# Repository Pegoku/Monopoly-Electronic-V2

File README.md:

# Monopoly-Electronic-V2
This is a recreation of the classic Monopoly Electronic Banking game using modern technology. The project utilizes an ESP32 microcontroller to handle game logic and interactions, along with a Touch LCD display and RFID readers for player identification and transactions.

## Demo

[Demo Video](https://youtube.com/shorts/_shUK3fcT8k?feature=share)

## Images

### Final product

### CAD

<details>
<summary>Xray view - click to expand</summary>

</details>

### PCB

<details>
<summary>Schematic - click to expand</summary>

</details>

## Features
- Electronic banking system using RFID cards for a more reliable process.
- Support for multiple players with individual RFID cards.
- Real-time game state updates displayed on the LCD.
- Sound effects for an immersive gaming experience.
- Customizable game rules and settings.

## UI

### Player registration

### Main game screen

### Card interaction

## How the Game Works

Gameplay focuses on **NFC interaction instead of menus**.

Players throw the dice, and depending on where they land, they interact with the game console using their RFID cards. For example, if a player lands on a property, they can use their card to purchase it, or pay rent.

The game keeps track of each player's balance and properties, and updates the display accordingly. The use of RFID cards allows for a more seamless and engaging gaming experience, as players can quickly and easily interact with the game without navigating through complex menus. 

When a player has not enough money to pay rent or buy a property, they can choose to mortgage their properties or declare bankruptcy. The game will automatically handle these situations and update the game state accordingly.

If a player doesn't have enough money to pay rent, they will be bankrupt and removed from the game. The last player remaining with money wins the game.

### Card programming

To program the RFID cards, you can use the programming mode in the game console. Simply press the two side buttons simultaneously for 10 seconds to enter programming mode. Then, place the card you want to program on the console and follow the prompts on the LCD display to assign a player name, land.

## BOM (Bill of Materials)
| Index | MPN                      | Description                                          | pack quantity | price | TOTAL  |
| ----- | ------------------------ | ---------------------------------------------------- | ------------- | ----- | ------ |
| 1     | BQ25895RTWR              | IC BATT CHG LI-ION 1CELL 24WQFN                      | 2             | 6.58  | 178.39 |
| 2     | TPS62162DSGR             | IC REG BUCK 3.3V 1A 8WSON                            | 2             | 3.14  |        |
| 3     | RCLAMP7522T.TNT          | TVS DIODE 5VWM 25VC SLP1007N5T                       | 2             | 3.14  |        |
| 4     | ESP32-S3-WROOM-1-N8R8    | RF TXRX MOD BT WIFI PCB TH SMD                       | 2             | 12.26 |        |
| 5     | NFC RFID Wireless Module | https://es.aliexpress.com/item/1005006837891461.html | 1             | 4.45  |        |
| 6     | MF1 1k NFC card          | https://es.aliexpress.com/item/1005006127590709.html | 50            | 12.91 |        |
| 7     | 1043P                    | BATTERY HOLDER 18650 PC PIN                          | 2             | 5.62  |        |
| 8     | F51L-1A7H1-11020         | CONN FFC FPC BOTTOM 20POS 1MM RA                     | 2             | 1.12  |        |
| 9     | 10155435-00011LF         | USB TYPE C R/A SMT 16PIN                             | 2             | 1.56  |        |
| 10    | NSR10F20NXT5G            | DIODE SCHOTTKY 20V 1A 2DSN                           | 2             | 0.3   |        |
| 11    | SM5817PL-TP              | DIODE SCHOTTKY 20V 1A SOD123FL                       | 3             | 0.45  |        |
| 12    | BLM21PG221SN1D           | FERRITE BEAD 220 OHM 0805 1LN                        | 3             | 0.33  |        |
| 13    | GRM21BR61C106KE15K       | CAP CER 10UF 16V X5R 0805                            | 10            | 0.81  |        |
| 14    | GRM21BR61A226ME51L       | CAP CER 22UF 10V X5R 0805                            | 10            | 1.14  |        |
| 15    | GRM188R72A104KA35D       | CAP CER 0.1UF 100V X7R 0603                          | 17            | 1.48  |        |
| 16    | 104CDMCCDS-220MC         | FIXED IND 22UH 5A 66 MOHM SMD                        | 2             | 1.6   |        |
| 17    | 74404054022              | FIXED IND 2.2UH 3.8A 19 MOHM SMD                     | 2             | 2.4   |        |
| 18    | 104CDMCCDS-2R2MC         | FIXED IND 2.2UH 15A 7 MOHM SMD                       | 2             | 1.6   |        |
| 19    | SRP4020TA-2R2M           | FIXED IND 2.2UH 4A 61 MOHM SMD                       | 2             | 2.04  |        |
| 20    | BC847B                   | TRANS NPN 45V 0.1A SOT23-3                           | 4             | 0.44  |        |
| 21    | CL10B105KP8NNNC          | CAP CER 1UF 10V X7R 0603                             | 11            | 0.06  |        |
| 22    | GRM188Z71A475ME15D       | CAP CER 4.7UF 10V X7R 0603                           | 11            | 1.34  |        |
| 23    | GRM188Z71A475ME15D       | CAP CER 4.7UF 10V X7R 0603                           | 11            | 1.34  |        |
| 24    | GRM1555C1H221JA01D       | CAP CER 220PF 50V C0G/NP0 0402                       | 11            | 0.36  |        |
| 25    | GCJ188R71H473KA12D       | CAP CER 0.047UF 50V X7R 0603                         | 11            | 0.96  |        |
| 26    | GRM155R71E473KA88D       | CAP CER 0.047UF 25V X7R 0402                         | 10            | 0.22  |        |
| 27    | ERJ-3EKF1004V            | RES SMD 1M OHM 1% 1/10W 0603                         | 11            | 0.37  |        |
| 28    | ERJ-PA3F5101V            | RES SMD 5.1K OHM 1% 1/3W 0603                        | 11            | 0.75  |        |
| 29    | ERJ-PA3F1003V            | RES SMD 100K OHM 1% 1/3W 0603                        | 11            | 0.75  |        |
| 30    | ERJ-PA3F4701V            | RES SMD 4.7K OHM 1% 1/3W 0603                        | 11            | 0.75  |        |
| 31    | ERJ-PA3F2201V            | RES SMD 2.2K OHM 1% 1/3W 0603                        | 11            | 0.75  |        |
| 32    | ERJ-PA3F1002V            | RES SMD 10K OHM 1% 1/3W 0603                         | 11            | 0.75  |        |
| 33    | ERJ-3EKF5231V            | RES SMD 5.23K OHM 1% 1/10W 0603                      | 11            | 0.37  |        |
| 34    | ERJ-PB3D3012V            | RES SMD 30.1K OHM 0.5% 1/5W 0603                     | 11            | 0.81  |        |
| 35    | ERJ-3EKF1202V            | RES SMD 12K OHM 1% 1/10W 0603                        | 11            | 0.37  |        |
| 36    | ERJ-3EKF22R0V            | RES SMD 22 OHM 1% 1/10W 0603                         | 11            | 0.37  |        |
| 37    | NCU18XH103F6SRB          | THERMISTOR NTC 10KOHM 3380K 0603                     | 2             | 0.28  |        |
| 38    | TL1105BF160Q             | SWITCH TACTILE SPST-NO 0.05A 12V                     | 6             | 1.2   |        |
| 39    | SKRPABE010               | SWITCH TACTILE SPST-NO 0.05A 16V                     | 4             | 0.84  |        |
| 40    | SLR-56VRT32              | LED RED DIFFUSED T-1 3/4 T/H                         | 3             | 1.59  |        |
| 41    | AO3400A                  | 30V 5.8A 35MR@10V,5.8A 1.4W 1.4V                     | 3             | 0.54  |        |
| 42    | AO3401A                  | 30V 4.1A 65MR@10V,4.2A 350MW 1.3                     | 3             | 0.6   |        |
| 43    | Rubber Feets             | https://es.aliexpress.com/item/1005007247599206.html | 4             | 3.22  |        |
| 44    | PCB                      | JLCPCB                                               | 1             | 41.59 |        |
| 45    | M3x16 (DIN912)           | https://es.aliexpress.com/item/1005007118809249.html | 55            | 4.67  |        |
| 46    | M2.5x6 (DIN7991)         | https://es.aliexpress.com/item/1005007118809249.html | 55            | 4.19  |        |
| 47    | heatset inserts M2.5x3.5 | https://es.aliexpress.com/item/1005007342105110.html | 50            | 3.4   |        |
| 48    | heatset inserts M3x4.2   | https://es.aliexpress.com/item/1005007342105110.html | 50            | 3.92  |        |
| 49    | 8R 0.5W 40mm Speaker     | https://es.aliexpress.com/item/1005007949154095.html | 1             | 3.51  |        |
| 50    | 3.2" ST7789 with touch   | https://es.aliexpress.com/item/1005009929917954.html | 1             | 10.37 |        |
| 51    | heatset insert pinecil   | https://es.aliexpress.com/item/1005008145530885.html | 1             | 11.89 |        |
| 52    | Digikey VAT               |                                                       | 1             | 12.89 |        |

## License

This work is licensed under a
[Creative Commons Attribution-NonCommercial 4.0 International License][cc-by-nc].

[![CC BY-NC 4.0][cc-by-nc-image]][cc-by-nc]

[cc-by-nc]: https://creativecommons.org/licenses/by-nc/4.0/
[cc-by-nc-image]: https://licensebuttons.net/l/by-nc/4.0/88x31.png
[cc-by-nc-shield]: https://img.shields.io/badge/License-CC%20BY--NC%204.0-lightgrey.svg

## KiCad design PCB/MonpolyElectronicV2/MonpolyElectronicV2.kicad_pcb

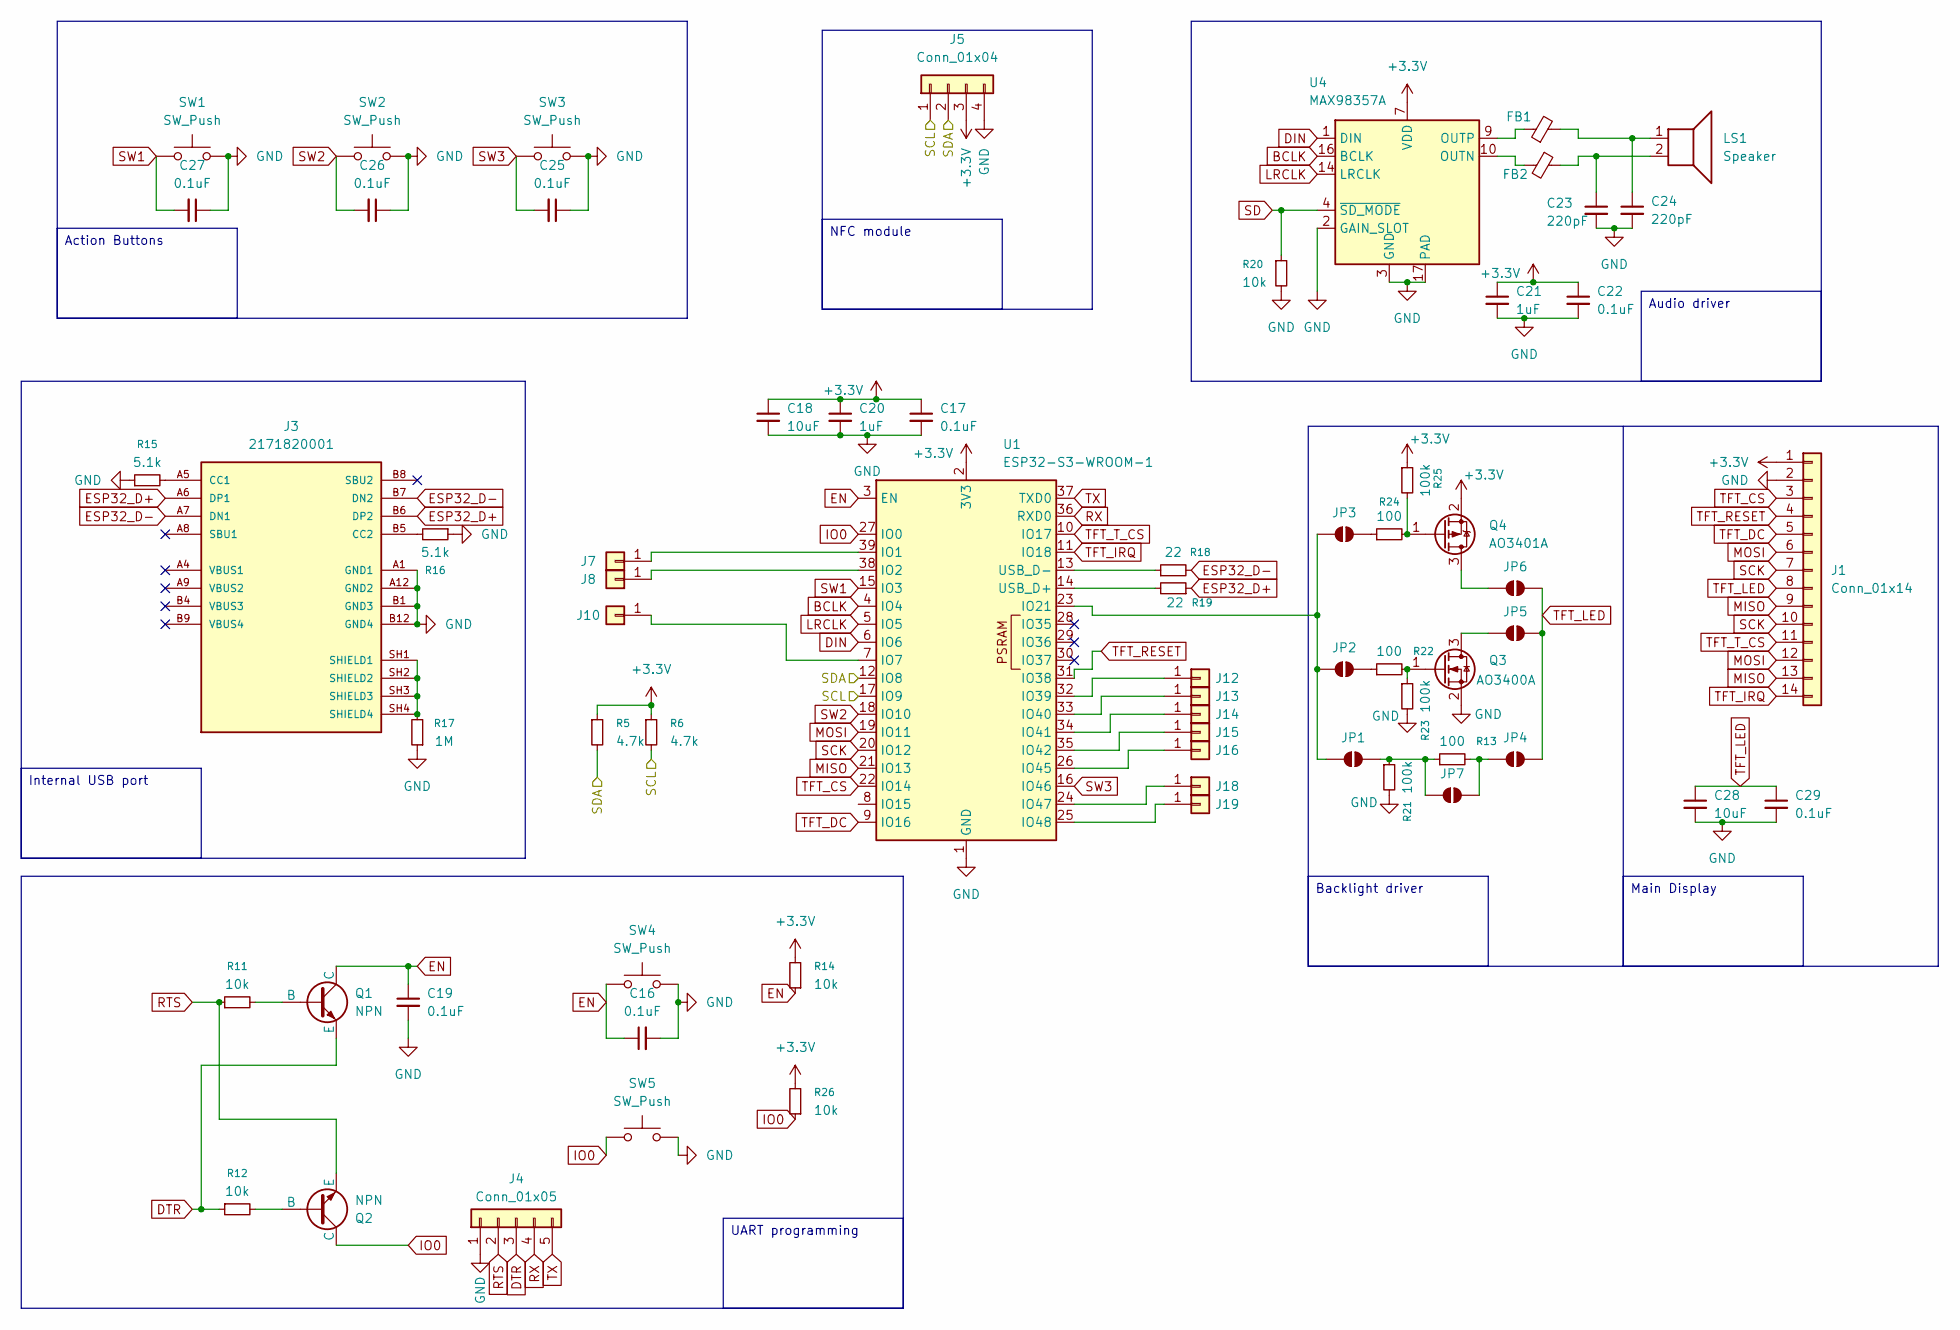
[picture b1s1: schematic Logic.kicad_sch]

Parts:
C16, C17, C19, C22, C25, C26, C27, C29: 0.1uF; C_0603_1608Metric
C18, C28: 10uF; C_0603_1608Metric
C20, C21: 1uF; C_0603_1608Metric
C23, C24: 220pF; C_0402_1005Metric
FB1, FB2: BLM21PG221SN1D; L_0805_2012Metric
J1: Conn_01x14; 240X320 TFT 3.2 display
J3: 2171820001; MOLEX_2171820001; PARTREV B
J4: Conn_01x05; PinHeader_1x05_P2.54mm_Vertical
J5: Conn_01x04; PinHeader_1x04_P2.54mm_Vertical
J7, J8, J10, J12, J13, J14, J15, J16, J18, J19: Conn_01x01; PinHeader_1x01_P2.54mm_Vertical
JP1, JP2, JP3, JP4, JP5, JP6, JP7: SolderJumper_2_Open; SolderJumper-2_P1.3mm_Open_TrianglePad1.0x1.5mm
LS1: Speaker; JST_XH_S2B-XH-A-1_1x02_P2.50mm_Horizontal
Q1, Q2: NPN; SOT-23-231
Q3: AO3400A; SOT-23
Q4: AO3401A; SOT-23
R5, R6: 4.7k; R_0603_1608Metric
R11, R12, R14, R20, R26: 10k; R_0603_1608Metric
R13, R22, R24: 100; R_0603_1608Metric
R15, R16: 5.1k; R_0603_1608Metric
R17: 1M; R_0603_1608Metric
R18, R19: 22; R_0603_1608Metric
R21, R23, R25: 100k; R_0603_1608Metric
SW1, SW2, SW3: SW_Push; SW_TL1105BF160Q
SW4, SW5: SW_Push; SW4_SKRPABE010_ALPS
U1: ESP32-S3-WROOM-1
U4: MAX98357A; TQFN-16-1EP_3x3mm_P0.5mm_EP1.23x1.23mm

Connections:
+3.3V: C17.1, C18.1, C20.1, C21.1, C22.1, J1.1, J5.3, Q4.2 (S), R5.1, R6.1, R14.2, R25.1, R26.2, U1.2 (3V3), U4.7 (VDD), U4.8 (VDD); also elsewhere on the board
/Logic/SCL: J5.1, R6.2, U1.17 (IO9); also elsewhere on the board
/Logic/SDA: J5.2, R5.2, U1.12 (IO8); also elsewhere on the board
BCLK: U1.4 (IO4), U4.16 (BCLK)
DIN: U1.6 (IO6), U4.1 (DIN)
DTR: J4.3, Q1.3 (E), R12.1
EN: C16.1, C19.1, Q1.1 (C), R14.1, SW4.1, U1.3 (EN)
ESP32_D+: J3.A6 (DP1), J3.B6 (DP2), R19.1
ESP32_D-: J3.A7 (DN1), J3.B7 (DN2), R18.2
GND: C16.2, C17.2, C18.2, C19.2, C20.2, C21.2, C22.2, C23.2, C24.2, C25.1, C26.1, C27.1, C28.2, C29.2, J1.2, J3.A1 (GND1), J3.A12 (GND2), J3.B1 (GND3), J3.B12 (GND4), J4.1, J5.4, Q3.2 (S), R15.1, R16.1, R17.1, R20.2, R21.2, R23.2, SW1.2, SW2.2, SW3.2, SW4.2, SW5.2, U1.1 (GND), U1.40 (GND), U1.41 (GND), U4.2 (GAIN_SLOT), U4.3 (GND), U4.11 (GND), U4.15 (GND), U4.17 (PAD); also elsewhere on the board
IO0: Q2.1 (C), R26.1, SW5.1, U1.27 (IO0)
LRCLK: U1.5 (IO5), U4.14 (LRCLK)
MISO: J1.9, J1.13, U1.21 (IO13)
MOSI: J1.6, J1.12, U1.19 (IO11)
unnamed: C23.1, FB2.1, LS1.2
unnamed: C24.1, FB1.2, LS1.1
unnamed: J3.A5 (CC1), R15.2
unnamed: J3.B5 (CC2), R16.2
unnamed: J3.SH1 (SHIELD1), J3.SH2 (SHIELD2), J3.SH3 (SHIELD3), J3.SH4 (SHIELD4), R17.2
unnamed: J7.1, U1.39 (IO1)
unnamed: J8.1, U1.38 (IO2)
unnamed: J10.1, U1.7 (IO7)
unnamed: J12.1, U1.32 (IO39)
unnamed: J13.1, U1.33 (IO40)
unnamed: J14.1, U1.34 (IO41)
unnamed: J15.1, U1.35 (IO42)
unnamed: J16.1, U1.26 (IO45)
unnamed: J18.1, U1.24 (IO47)
unnamed: J19.1, U1.25 (IO48)
unnamed: JP1.1 (A), JP7.2 (B), R13.1, R21.1
unnamed: JP1.2 (B), JP2.2 (B), JP3.2 (B), U1.23 (IO21)
unnamed: JP2.1 (A), R22.1
unnamed: JP3.1 (A), R24.1
unnamed: JP4.2 (B), JP7.1 (A), R13.2
unnamed: JP5.2 (B), Q3.3 (D)
unnamed: JP6.2 (B), Q4.3 (D)
unnamed: Q1.2 (B), R11.2
unnamed: Q2.2 (B), R12.2
unnamed: Q3.1 (G), R22.2, R23.1
unnamed: Q4.1 (G), R24.2, R25.2
unnamed: R19.2, U1.14 (USB_D+)
unnamed: R18.1, U1.13 (USB_D-)
unnamed: FB2.2, U4.10 (OUTN)
unnamed: FB1.1, U4.9 (OUTP)
RTS: J4.2, Q2.3 (E), R11.1
RX: J4.4, U1.36 (RXD0)
SCK: J1.7, J1.10, U1.20 (IO12)
SD: R20.1, U4.4 (~SD_MODE)
SW1: C27.2, SW1.1, U1.15 (IO3)
SW2: C26.2, SW2.1, U1.18 (IO10)
SW3: C25.2, SW3.1, U1.16 (IO46)
TFT_CS: J1.3, U1.22 (IO14)
TFT_DC: J1.5, U1.9 (IO16)
TFT_IRQ: J1.14, U1.11 (IO18)
TFT_LED: C28.1, C29.1, J1.8, JP4.1 (A), JP5.1 (A), JP6.1 (A)
TFT_RESET: J1.4, U1.31 (IO38)
TFT_T_CS: J1.11, U1.10 (IO17)
TX: J4.5, U1.37 (TXD0)

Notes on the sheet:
Internal USB port
Main Display
Audio driver
UART programming
Backlight driver
Action Buttons
NFC module

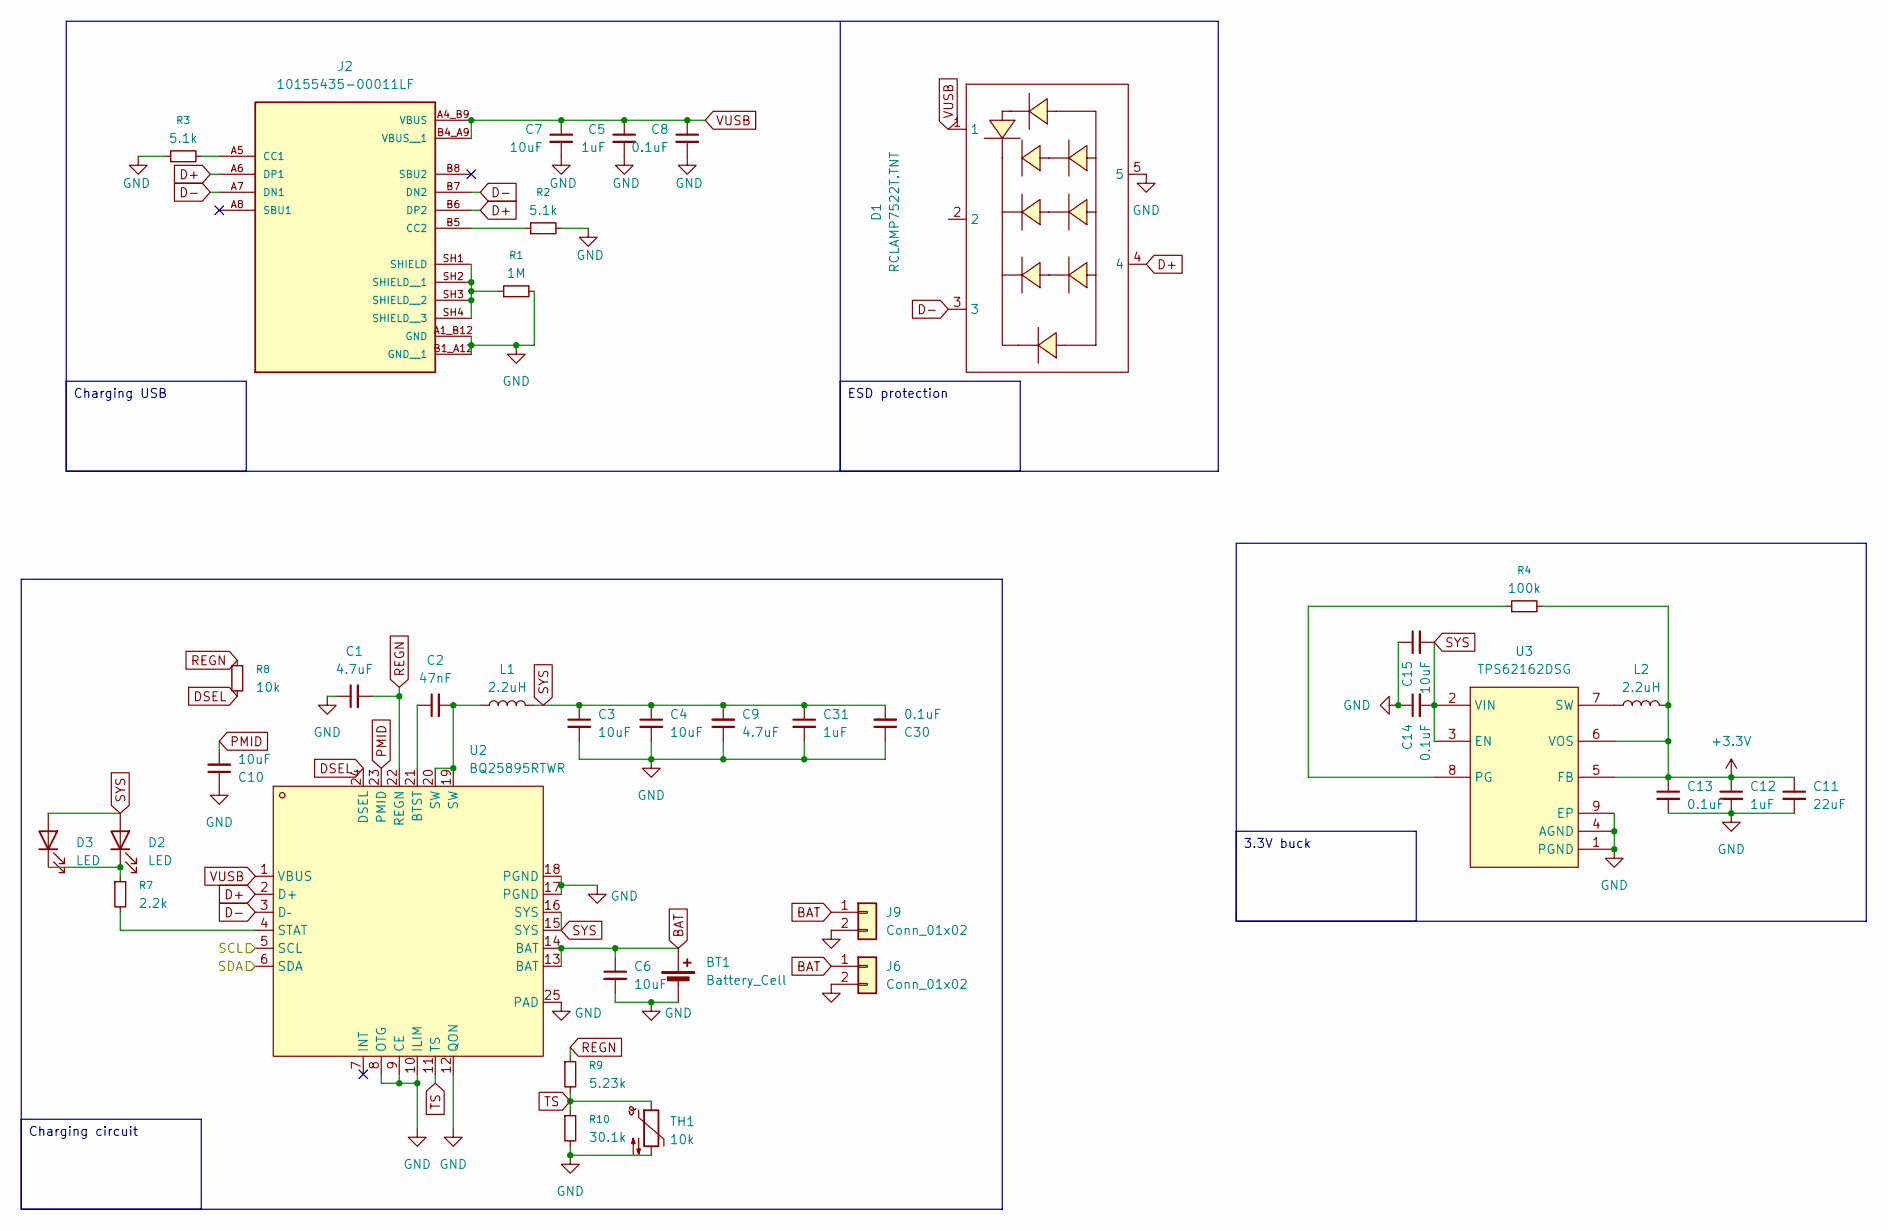
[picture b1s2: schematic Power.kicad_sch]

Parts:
BT1: Battery_Cell; BAT-TH_1043P
C1, C9: 4.7uF; C_0603_1608Metric
C2: 47nF; C_0402_1005Metric
C3, C4, C6, C7, C10, C15: 10uF; C_0805_2012Metric
C5, C12, C31: 1uF; C_0603_1608Metric
C8, C13, C14, C30: 0.1uF; C_0603_1608Metric
C11: 22uF; C_0805_2012Metric
D1: RCLAMP7522T.TNT; SLP1007N5T_L1.0-W0.7-P0.35-BL; LCSC Part C1977186
D2: LED; LED_0603_1608Metric
D3: LED; LED_D5.0mm_Horizontal_O1.27mm_Z3.0mm
J2: 10155435-00011LF; AMPHENOL_10155435-00011LF; PARTREV C
J6: Conn_01x02; JST_XH_B2B-XH-A_1x02_P2.50mm_Vertical
J9: Conn_01x02; PinHeader_1x02_P2.54mm_Vertical
L1: 2.2uH; IND_SRP4020TA_BRN
L2: 2.2uH; WE-LQS_5040
R1: 1M; R_0603_1608Metric
R2, R3: 5.1k; R_0603_1608Metric
R4: 100k; R_0603_1608Metric
R7: 2.2k; R_0603_1608Metric
R8: 10k; R_0603_1608Metric
R9: 5.23k; R_0603_1608Metric
R10: 30.1k; R_0603_1608Metric
TH1: 10k; R_0603_1608Metric
U2: BQ25895RTWR; QFN-24_L4.0-W4.0-P0.50-TL-EP2.7; LCSC Part C80200
U3: TPS62162DSG; WSON-8_L2.0-W2.0-P0.50-TL-EP; LCSC Part C40256

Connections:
+3.3V: C11.1, C12.1, C13.1, L2.2, R4.2, U3.5 (FB), U3.6 (VOS); also elsewhere on the board
/Logic/SCL: U2.5 (SCL); also elsewhere on the board
/Logic/SDA: U2.6 (SDA); also elsewhere on the board
BAT: BT1.1 (+), C6.1, J6.1, J9.1, U2.13 (BAT), U2.14 (BAT)
D+: D1.4, J2.A6 (DP1), J2.B6 (DP2), U2.2 (D+)
D-: D1.3, J2.A7 (DN1), J2.B7 (DN2), U2.3 (D–)
DSEL: R8.2, U2.24 (DSEL)
GND: BT1.2 (-), C1.1, C3.2, C4.2, C5.2, C6.2, C7.2, C8.2, C9.1, C10.1, C11.2, C12.2, C13.2, C14.1, C15.1, C30.1, C31.2, D1.5, J2.A1_B12 (GND), J2.B1_A12 (GND__1), J6.2, J9.2, R1.2, R2.2, R3.1, R10.2, TH1.2, U2.8 (OTG), U2.9 (CE), U2.10 (ILIM), U2.12 (QON), U2.17 (PGND), U2.18 (PGND), U2.25 (PAD), U3.1 (PGND), U3.4 (AGND), U3.9 (EP); also elsewhere on the board
unnamed: C2.2, L1.1, U2.19 (SW), U2.20 (SW)
unnamed: D2.1 (K), D3.1 (K), R7.1
unnamed: J2.A5 (CC1), R3.2
unnamed: J2.B5 (CC2), R2.1
unnamed: J2.SH1 (SHIELD), J2.SH2 (SHIELD__1), J2.SH3 (SHIELD__2), J2.SH4 (SHIELD__3), R1.1
unnamed: C2.1, U2.21 (BTST)
unnamed: R7.2, U2.4 (STAT)
unnamed: R4.1, U3.8 (PG)
unnamed: L2.1, U3.7 (SW)
PMID: C10.2, U2.23 (PMID)
REGN: C1.2, R8.1, R9.1, U2.22 (REGN)
SYS: C3.1, C4.1, C9.2, C14.2, C15.2, C30.2, C31.1, D2.2 (A), D3.2 (A), L1.2, U2.15 (SYS), U2.16 (SYS), U3.2 (VIN), U3.3 (EN)
TS: R9.2, R10.1, TH1.1, U2.11 (TS)
VUSB: C5.1, C7.1, C8.1, D1.1, J2.A4_B9 (VBUS), J2.B4_A9 (VBUS__1), U2.1 (VBUS)

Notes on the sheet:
Charging USB
ESD protection
Charging circuit
3.3V buck

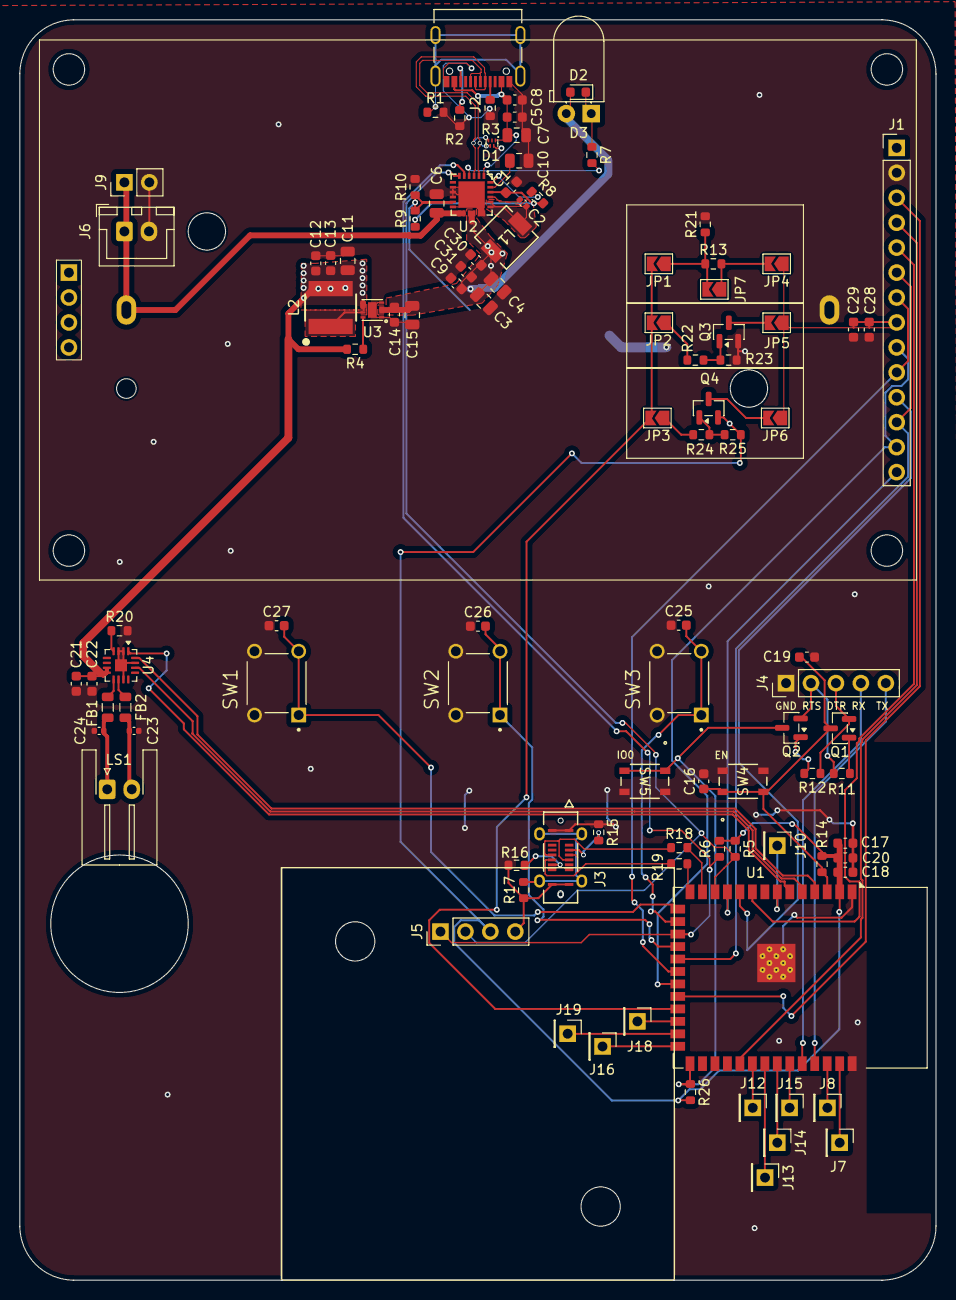
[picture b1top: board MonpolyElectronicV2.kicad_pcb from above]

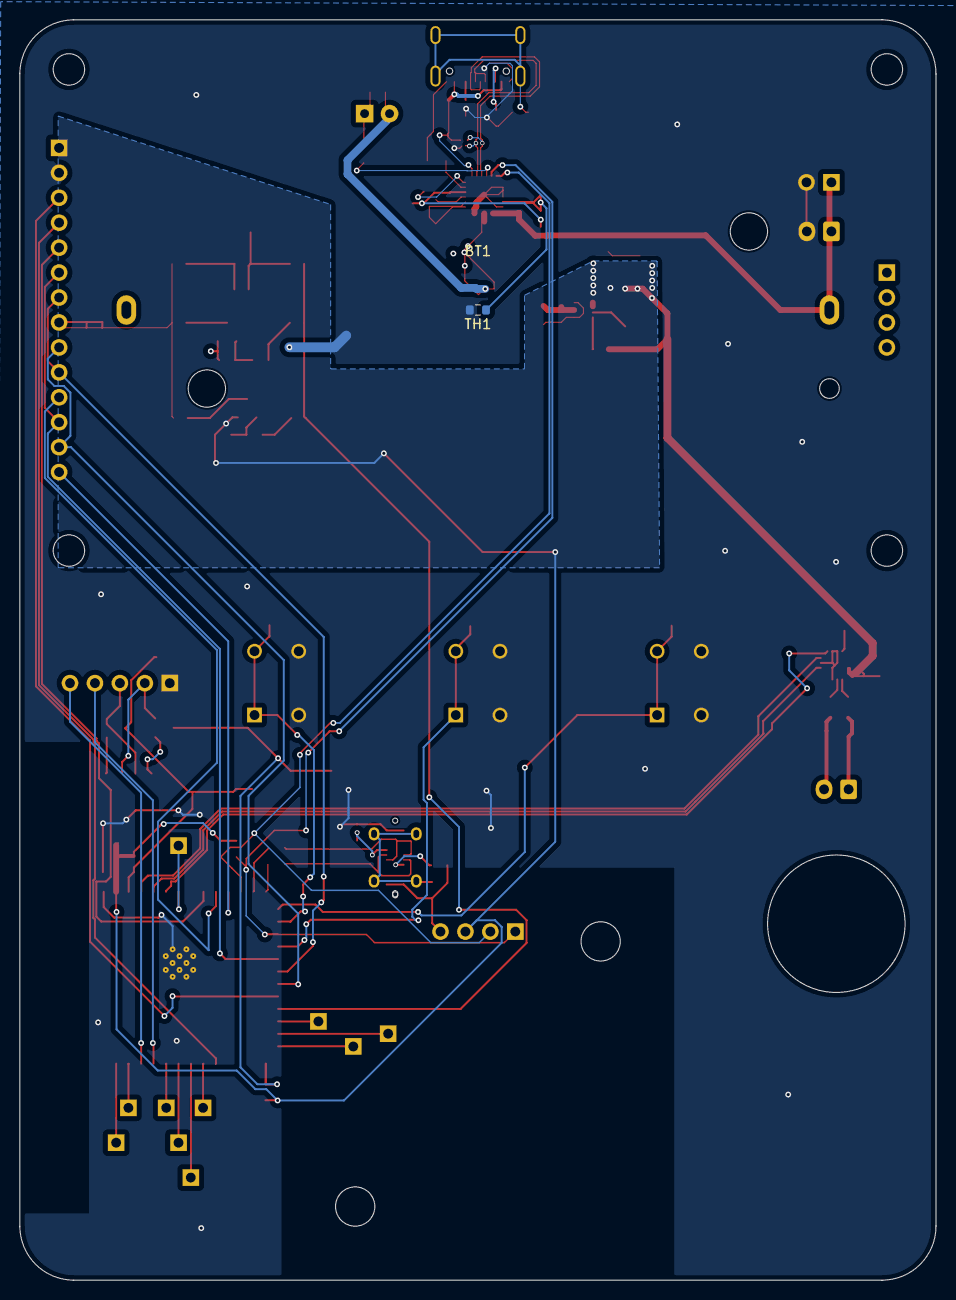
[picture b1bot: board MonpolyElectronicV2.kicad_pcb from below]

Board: 2 copper layers, 93.3 x 128.3 mm, 104 parts (2 on the bottom side), 76 nets.

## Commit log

2025-10-03 Add GNU Lesser General Public License v2.1
    Added the GNU Lesser General Public License version 2.1 to the project.
2025-10-04 Place most parts and start Power schematic
2025-10-06 continue battery circuit. Finished BQ25895RTWR and USB wiring
2025-10-06 work on Logic part (MCU): audio done, programming done, ESP32 and inputs WIP, diplay not yet started
2025-10-07 find possible display
2025-10-08 Finish Schematic wiring
2025-10-08 Start adding footprints
2025-10-10 add symbols + multiple backlight options
2025-10-10 assign footprints + multiple backlight options
2025-10-10 add decoupling caps to TFT B_LED
2025-10-11 Add boxes to schematic
2025-10-11 fix DTR and RTS circuit
2025-10-11 Start component placing by groups: BQ25895RTWR, TPS62162DSG and 10155435-00011LF done
2025-10-11 finish placement of all components
2025-10-11 finish placing components
2025-10-12 start routing top part of the pcb
2025-10-13 Finish routing PCB
2025-10-13 start CAD
2025-10-15 CAD base start
2025-10-15 continue CAD
2025-10-15 base done
2025-10-15 continue on the cover, and design clipping mechanism
2025-10-17 Finish CAD (hopefully)
2025-10-17 battery tab
2025-10-17 finish cad FR this time
2025-10-18 get repo ready
2025-10-18 update BOM
2025-10-18 update BOM, again
2025-10-19 Code for LVGL (used to test the display)
2025-10-30 display test
2025-10-31 IRQ touch test
2026-02-10 code uploads
2026-02-10 UI v1
2026-02-10 fix text not displaying
2026-02-10 v2 ui
2026-02-10 fix orientation
2026-02-11 v2.1 ui
2026-02-11 v2.2 ui
2026-02-11 v2.3 ui
2026-02-11 v2.4 ui
2026-02-14 WIP: espCodev3
2026-02-14 non-blocking display
2026-02-14 fix display not updating
2026-02-14 improvements
2026-02-15 dark theme
2026-02-15 use hardware SPI for faster redraw
2026-02-15 card generator WEB
2026-03-02 update cards
2026-03-02 fix cards and some logic
2026-03-02 reduce display speed
2026-03-04 finish
